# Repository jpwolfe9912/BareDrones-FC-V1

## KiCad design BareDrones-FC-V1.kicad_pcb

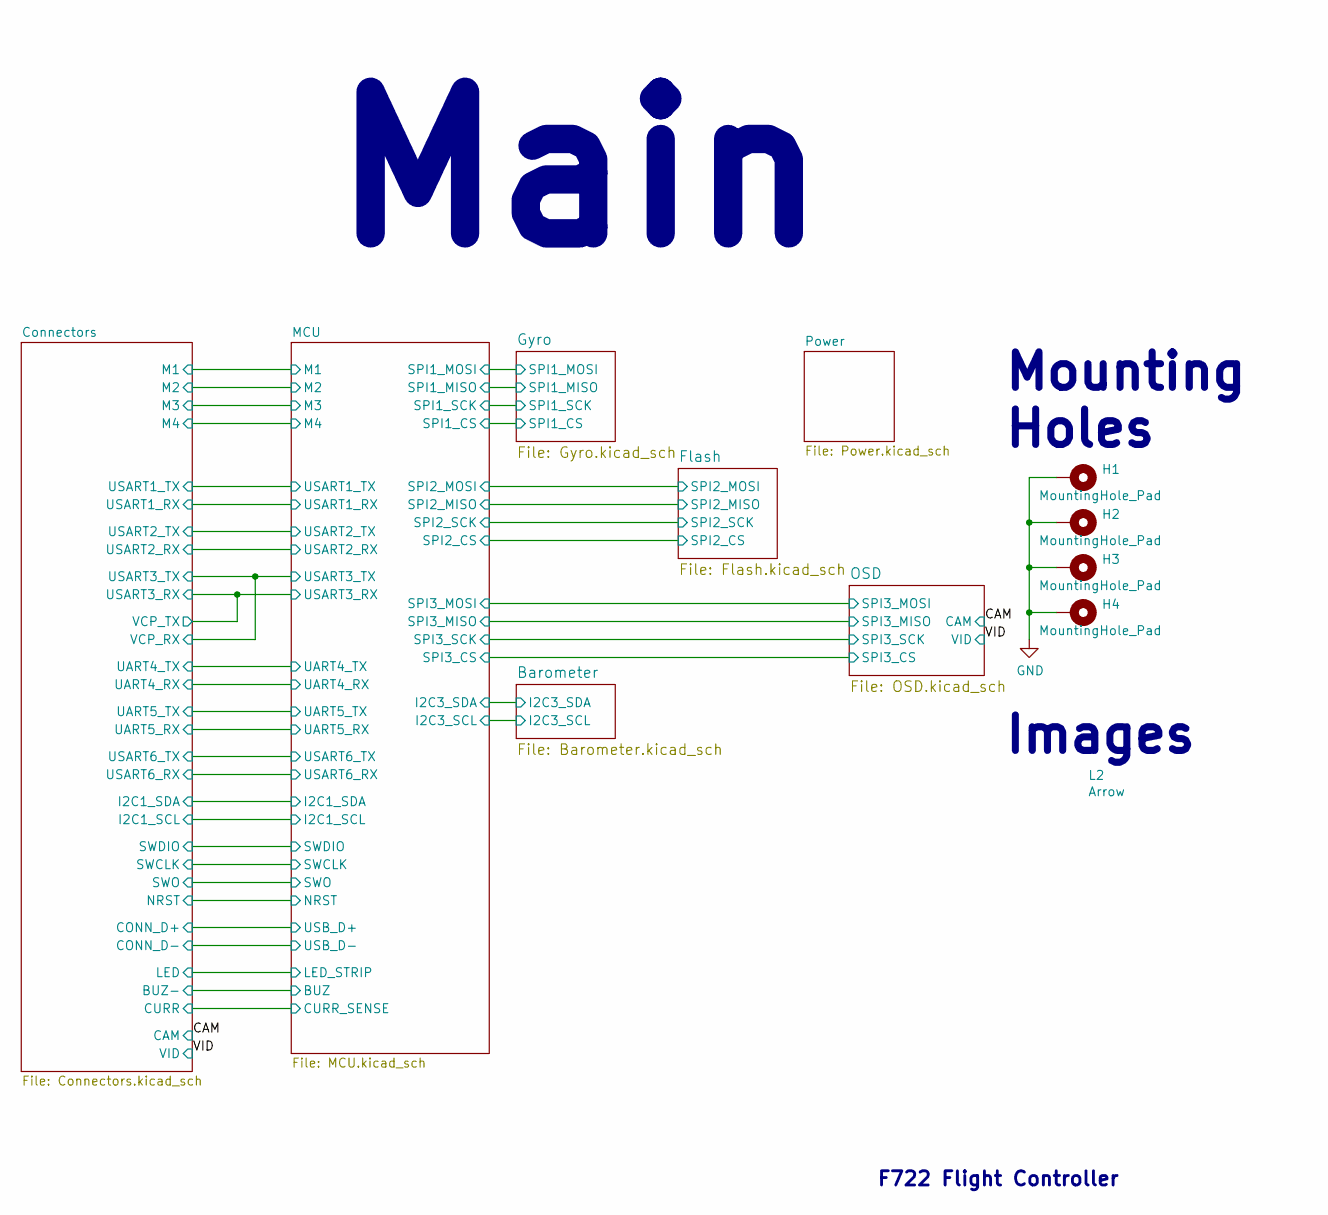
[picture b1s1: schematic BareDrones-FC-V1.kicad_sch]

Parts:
H1, H2, H3, H4: MountingHole_Pad; M3_Mounting_Hole
L1: EGA
L2: Arrow

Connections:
GND: H1.1, H2.1, H3.1, H4.1; also elsewhere on the board

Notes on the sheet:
F722 Flight Controller
Mounting Holes
Main
Images

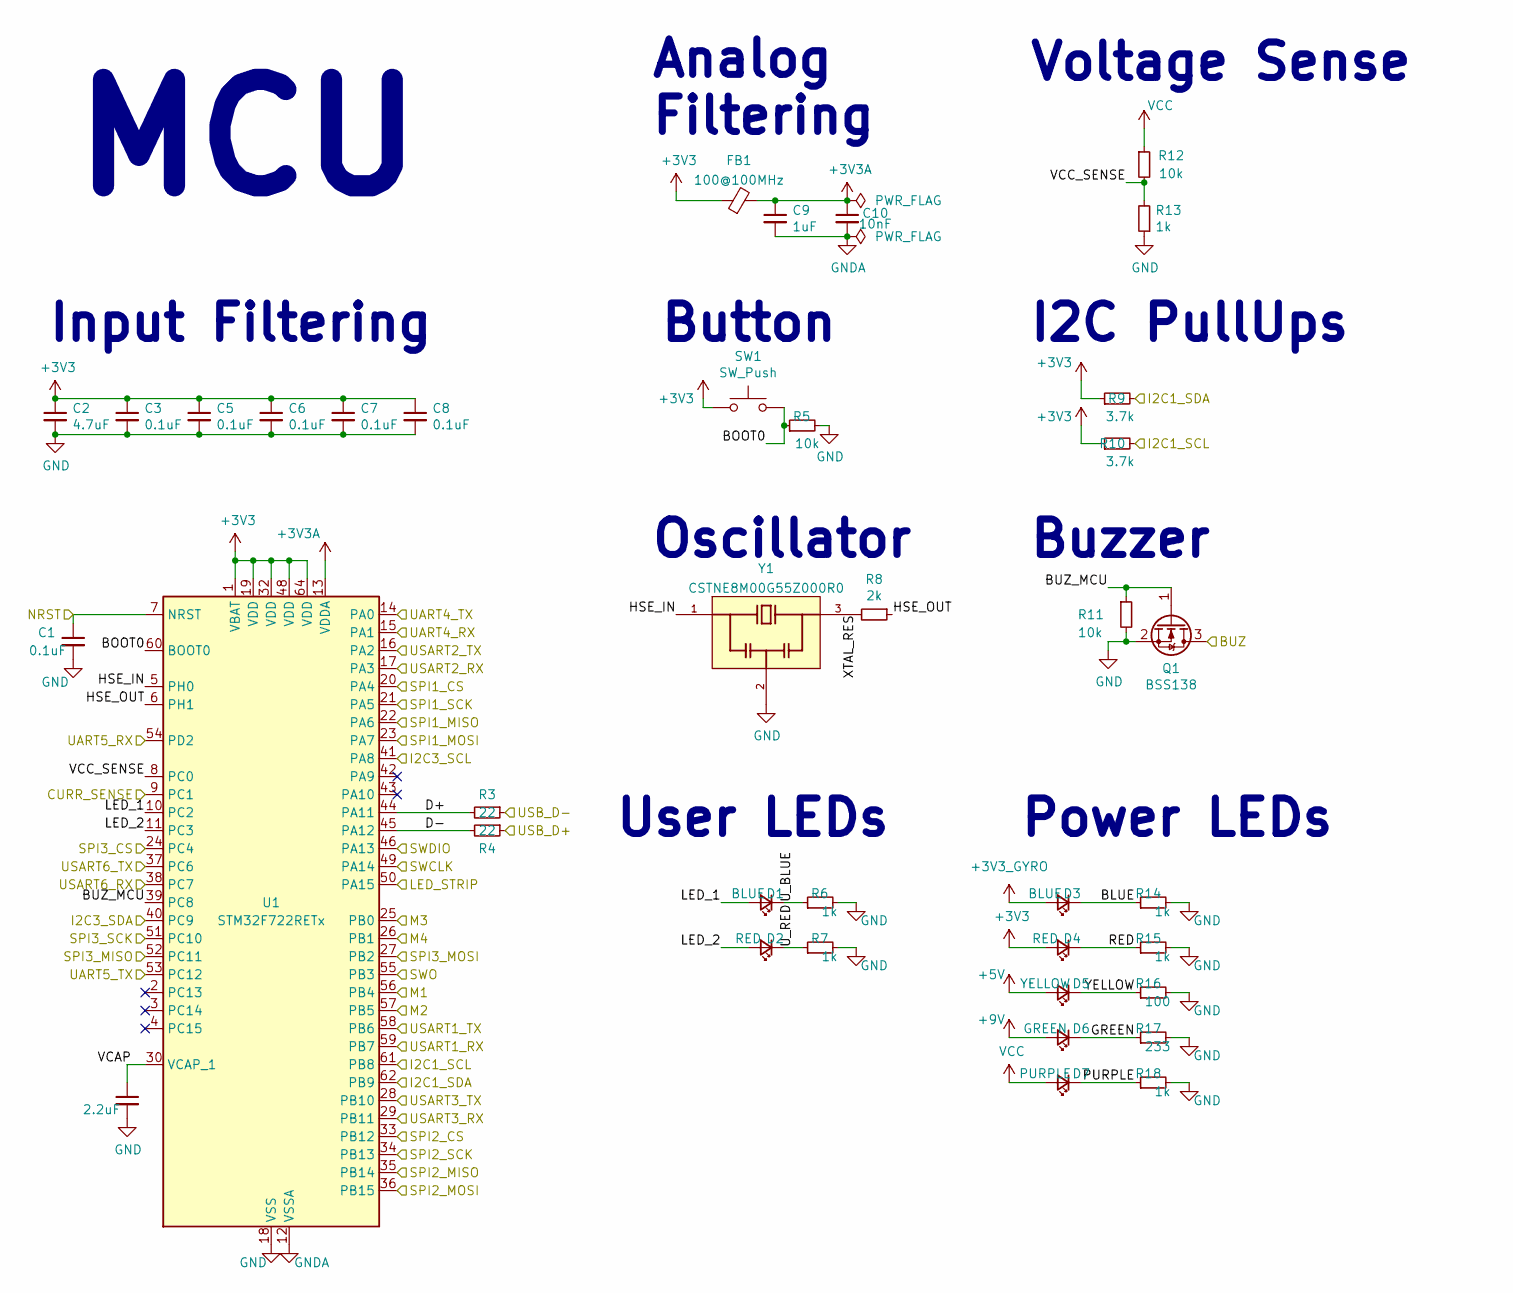
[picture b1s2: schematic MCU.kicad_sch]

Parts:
C1, C3, C5, C6, C7, C8: 0.1uF; C_0402_1005Metric
C2: 4.7uF; C_0402_1005Metric
C4: 2.2uF; C_0402_1005Metric
C9: 1uF; C_0402_1005Metric
C10: 10nF; C_0402_1005Metric
D1, D3: BLUE; LED_0603_1608Metric
D2, D4: RED; LED_0603_1608Metric
D5: YELLOW; LED_0603_1608Metric
D6: GREEN; LED_0603_1608Metric
D7: PURPLE; LED_0603_1608Metric
FB1: 100@100MHz; L_0603_1608Metric
Q1: BSS138; SOT-23
R3, R4: 22; R_0402_1005Metric
R5, R11, R12: 10k; R_0402_1005Metric
R6, R7, R13, R14, R15, R18: 1k; R_0402_1005Metric
R8: 2k; R_0402_1005Metric
R9, R10: 3.7k; R_0402_1005Metric
R16: 100; R_0402_1005Metric
R17: 233; R_0402_1005Metric
SW1: SW_Push; SW_SPST_B3U-1000P
U1: STM32F722RETx; LQFP-64_10x10mm_P0.5mm
Y1: CSTNE8M00G55Z000R0; OSC_CSTNE8M00G55Z000R0; PARTREV JGC42-8858A

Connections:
+3V3: C2.1, C3.1, C5.1, C6.1, C7.1, C8.1, D4.2 (A), FB1.1, R9.1, R10.1, SW1.1, U1.1 (VBAT), U1.19 (VDD), U1.32 (VDD), U1.48 (VDD), U1.64 (VDD); also elsewhere on the board
+3V3A: C9.1, C10.1, FB1.2, U1.13 (VDDA)
+3V3_GYRO: D3.2 (A); also elsewhere on the board
+5V: D5.2 (A); also elsewhere on the board
+9V: D6.2 (A); also elsewhere on the board
/Barometer/I2C3_SCL: U1.41 (PA8); also elsewhere on the board
/Barometer/I2C3_SDA: U1.40 (PC9); also elsewhere on the board
/Connectors/BUZ-: Q1.3 (D); also elsewhere on the board
/Connectors/CONN_D+: R4.1; also elsewhere on the board
/Connectors/CONN_D-: R3.1; also elsewhere on the board
/Connectors/CURR: U1.9 (PC1); also elsewhere on the board
/Connectors/I2C1_SCL: R10.2, U1.61 (PB8); also elsewhere on the board
/Connectors/I2C1_SDA: R9.2, U1.62 (PB9); also elsewhere on the board
/Connectors/LED: U1.50 (PA15); also elsewhere on the board
/Connectors/M1: U1.56 (PB4); also elsewhere on the board
/Connectors/M2: U1.57 (PB5); also elsewhere on the board
/Connectors/M3: U1.25 (PB0); also elsewhere on the board
/Connectors/M4: U1.26 (PB1); also elsewhere on the board
/Connectors/NRST: C1.1, U1.7 (NRST); also elsewhere on the board
/Connectors/SWCLK: U1.49 (PA14); also elsewhere on the board
/Connectors/SWDIO: U1.46 (PA13); also elsewhere on the board
/Connectors/SWO: U1.55 (PB3); also elsewhere on the board
/Connectors/UART4_RX: U1.15 (PA1); also elsewhere on the board
/Connectors/UART4_TX: U1.14 (PA0); also elsewhere on the board
/Connectors/UART5_RX: U1.54 (PD2); also elsewhere on the board
/Connectors/UART5_TX: U1.53 (PC12); also elsewhere on the board
/Connectors/USART1_RX: U1.59 (PB7); also elsewhere on the board
/Connectors/USART1_TX: U1.58 (PB6); also elsewhere on the board
/Connectors/USART2_RX: U1.17 (PA3); also elsewhere on the board
/Connectors/USART2_TX: U1.16 (PA2); also elsewhere on the board
/Connectors/USART3_RX: U1.29 (PB11); also elsewhere on the board
/Connectors/USART3_TX: U1.28 (PB10); also elsewhere on the board
/Connectors/USART6_RX: U1.38 (PC7); also elsewhere on the board
/Connectors/USART6_TX: U1.37 (PC6); also elsewhere on the board
/Flash/SPI2_CS: U1.33 (PB12); also elsewhere on the board
/Flash/SPI2_MISO: U1.35 (PB14); also elsewhere on the board
/Flash/SPI2_MOSI: U1.36 (PB15); also elsewhere on the board
/Flash/SPI2_SCK: U1.34 (PB13); also elsewhere on the board
/Gyro/SPI1_CS: U1.20 (PA4); also elsewhere on the board
/Gyro/SPI1_MISO: U1.22 (PA6); also elsewhere on the board
/Gyro/SPI1_MOSI: U1.23 (PA7); also elsewhere on the board
/Gyro/SPI1_SCK: U1.21 (PA5); also elsewhere on the board
/MCU/BLUE: D3.1 (K), R14.1
/MCU/BOOT0: R5.1, SW1.2, U1.60 (BOOT0)
/MCU/BUZ_MCU: Q1.1 (G), R11.1, U1.39 (PC8)
/MCU/D+: R3.2, U1.44 (PA11)
/MCU/D-: R4.2, U1.45 (PA12)
/MCU/GREEN: D6.1 (K), R17.1
/MCU/HSE_IN: U1.5 (PH0), Y1.1
/MCU/HSE_OUT: R8.1, U1.6 (PH1)
/MCU/LED_1: D1.2 (A), U1.10 (PC2)
/MCU/LED_2: D2.2 (A), U1.11 (PC3)
/MCU/PURPLE: D7.1 (K), R18.1
/MCU/RED: D4.1 (K), R15.1
/MCU/SPI3_CS: U1.24 (PC4); also elsewhere on the board
/MCU/SPI3_MISO: U1.52 (PC11); also elsewhere on the board
/MCU/SPI3_MOSI: U1.27 (PB2); also elsewhere on the board
/MCU/SPI3_SCK: U1.51 (PC10); also elsewhere on the board
/MCU/U_BLUE: D1.1 (K), R6.1
/MCU/U_RED: D2.1 (K), R7.1
/MCU/VCAP: C4.1, U1.30 (VCAP_1)
/MCU/VCC_SENSE: R12.2, R13.2, U1.8 (PC0)
/MCU/XTAL_RES: R8.2, Y1.3
/MCU/YELLOW: D5.1 (K), R16.1
GND: C1.2, C2.2, C3.2, C4.2, C5.2, C6.2, C7.2, C8.2, Q1.2 (S), R5.2, R6.2, R7.2, R11.2, R13.1, R14.2, R15.2, R16.2, R17.2, R18.2, U1.18 (VSS), U1.31 (VSS), U1.47 (VSS), U1.63 (VSS), Y1.2; also elsewhere on the board
GNDA: C9.2, C10.2, U1.12 (VSSA)
VCC: D7.2 (A), R12.1; also elsewhere on the board

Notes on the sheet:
MCU
User LEDs
Buzzer
Analog Filtering
Input Filtering
Oscillator
I2C PullUps
Button
Voltage Sense
Power LEDs

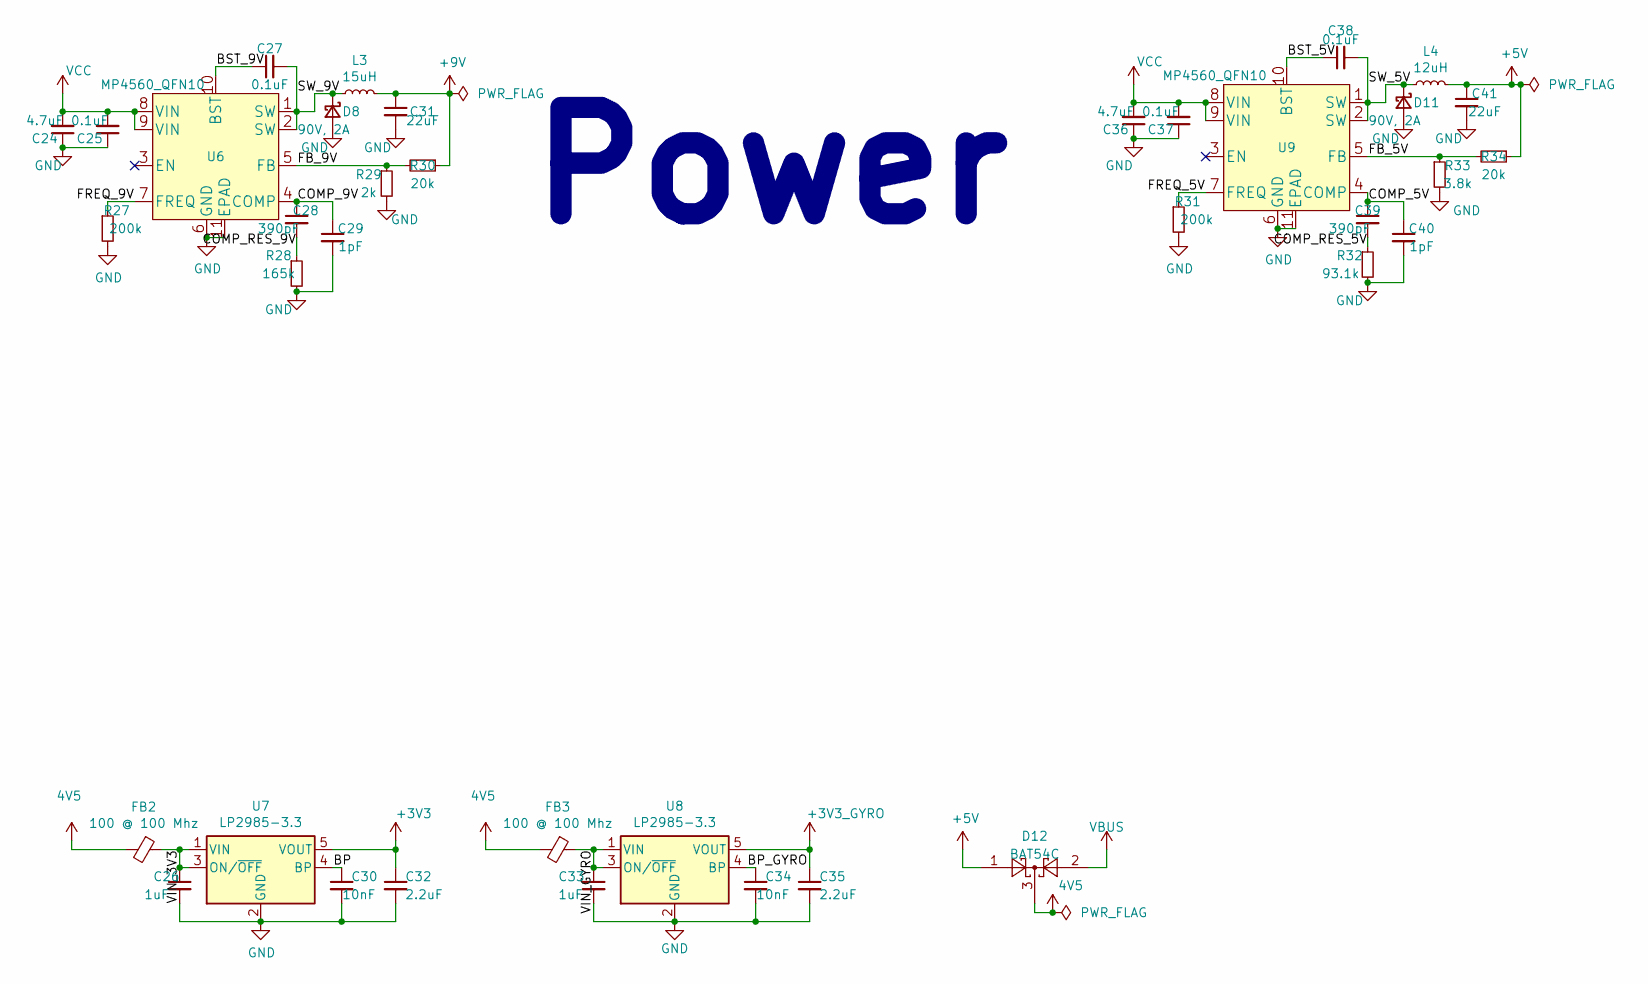
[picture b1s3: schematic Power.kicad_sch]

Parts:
C24, C36: 4.7uF; C_0402_1005Metric
C25, C27, C37, C38: 0.1uF; C_0402_1005Metric
C26, C33: 1uF; C_0402_1005Metric
C28, C39: 390pF; C_0402_1005Metric
C29, C40: 1pF; C_0402_1005Metric
C30, C34: 10nF; C_0402_1005Metric
C31, C41: 22uF; C_0402_1005Metric
C32, C35: 2.2uF; C_0402_1005Metric
D8, D11: 90V, 2A; D_SOD-523
D12: BAT54C; SOT-23
FB2, FB3: 100 @ 100 Mhz; L_0603_1608Metric
L3: 15uH; SRN3015-4R7M
L4: 12uH; SRN3015-4R7M
R27, R31: 200k; R_0402_1005Metric
R28: 165k; R_0402_1005Metric
R29: 2k; R_0402_1005Metric
R30, R34: 20k; R_0402_1005Metric
R32: 93.1k; R_0402_1005Metric
R33: 3.8k; R_0402_1005Metric
U6, U9: MP4560_QFN10; MP4560DQ
U7, U8: LP2985-3.3; SOT-23-5

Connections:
4V5: D12.3, FB2.2, FB3.2; also elsewhere on the board
+3V3: C32.1, U7.5 (VOUT); also elsewhere on the board
+3V3_GYRO: C35.1, U8.5 (VOUT); also elsewhere on the board
+5V: C41.1, D12.1, L4.2, R34.1; also elsewhere on the board
+9V: C31.1, L3.2, R30.1; also elsewhere on the board
/Power/BP: C30.1, U7.4 (BP)
/Power/BP_GYRO: C34.1, U8.4 (BP)
/Power/BST_5V: C38.1, U9.10 (BST)
/Power/BST_9V: C27.1, U6.10 (BST)
/Power/COMP_5V: C39.1, C40.1, U9.4 (COMP)
/Power/COMP_9V: C28.1, C29.1, U6.4 (COMP)
/Power/COMP_RES_5V: C39.2, R32.1
/Power/COMP_RES_9V: C28.2, R28.1
/Power/FB_5V: R33.1, R34.2, U9.5 (FB)
/Power/FB_9V: R29.1, R30.2, U6.5 (FB)
/Power/FREQ_5V: R31.1, U9.7 (FREQ)
/Power/FREQ_9V: R27.1, U6.7 (FREQ)
/Power/SW_5V: C38.2, D11.1 (K), L4.1, U9.1 (SW), U9.2 (SW)
/Power/SW_9V: C27.2, D8.1 (K), L3.1, U6.1 (SW), U6.2 (SW)
/Power/VIN_3V3: C26.1, FB2.1, U7.1 (VIN), U7.3 (ON/~OFF)
/Power/VIN_GYRO: C33.1, FB3.1, U8.1 (VIN), U8.3 (ON/~OFF)
GND: C24.1, C25.1, C26.2, C29.2, C30.2, C31.2, C32.2, C33.2, C34.2, C35.2, C36.1, C37.1, C40.2, C41.2, D8.2 (A), D11.2 (A), R27.2, R28.2, R29.2, R31.2, R32.2, R33.2, U6.6 (GND), U6.11 (EPAD), U7.2 (GND), U8.2 (GND), U9.6 (GND), U9.11 (EPAD); also elsewhere on the board
VBUS: D12.2; also elsewhere on the board
VCC: C24.2, C25.2, C36.2, C37.2, U6.8 (VIN), U6.9 (VIN), U9.8 (VIN), U9.9 (VIN); also elsewhere on the board

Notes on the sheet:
Power

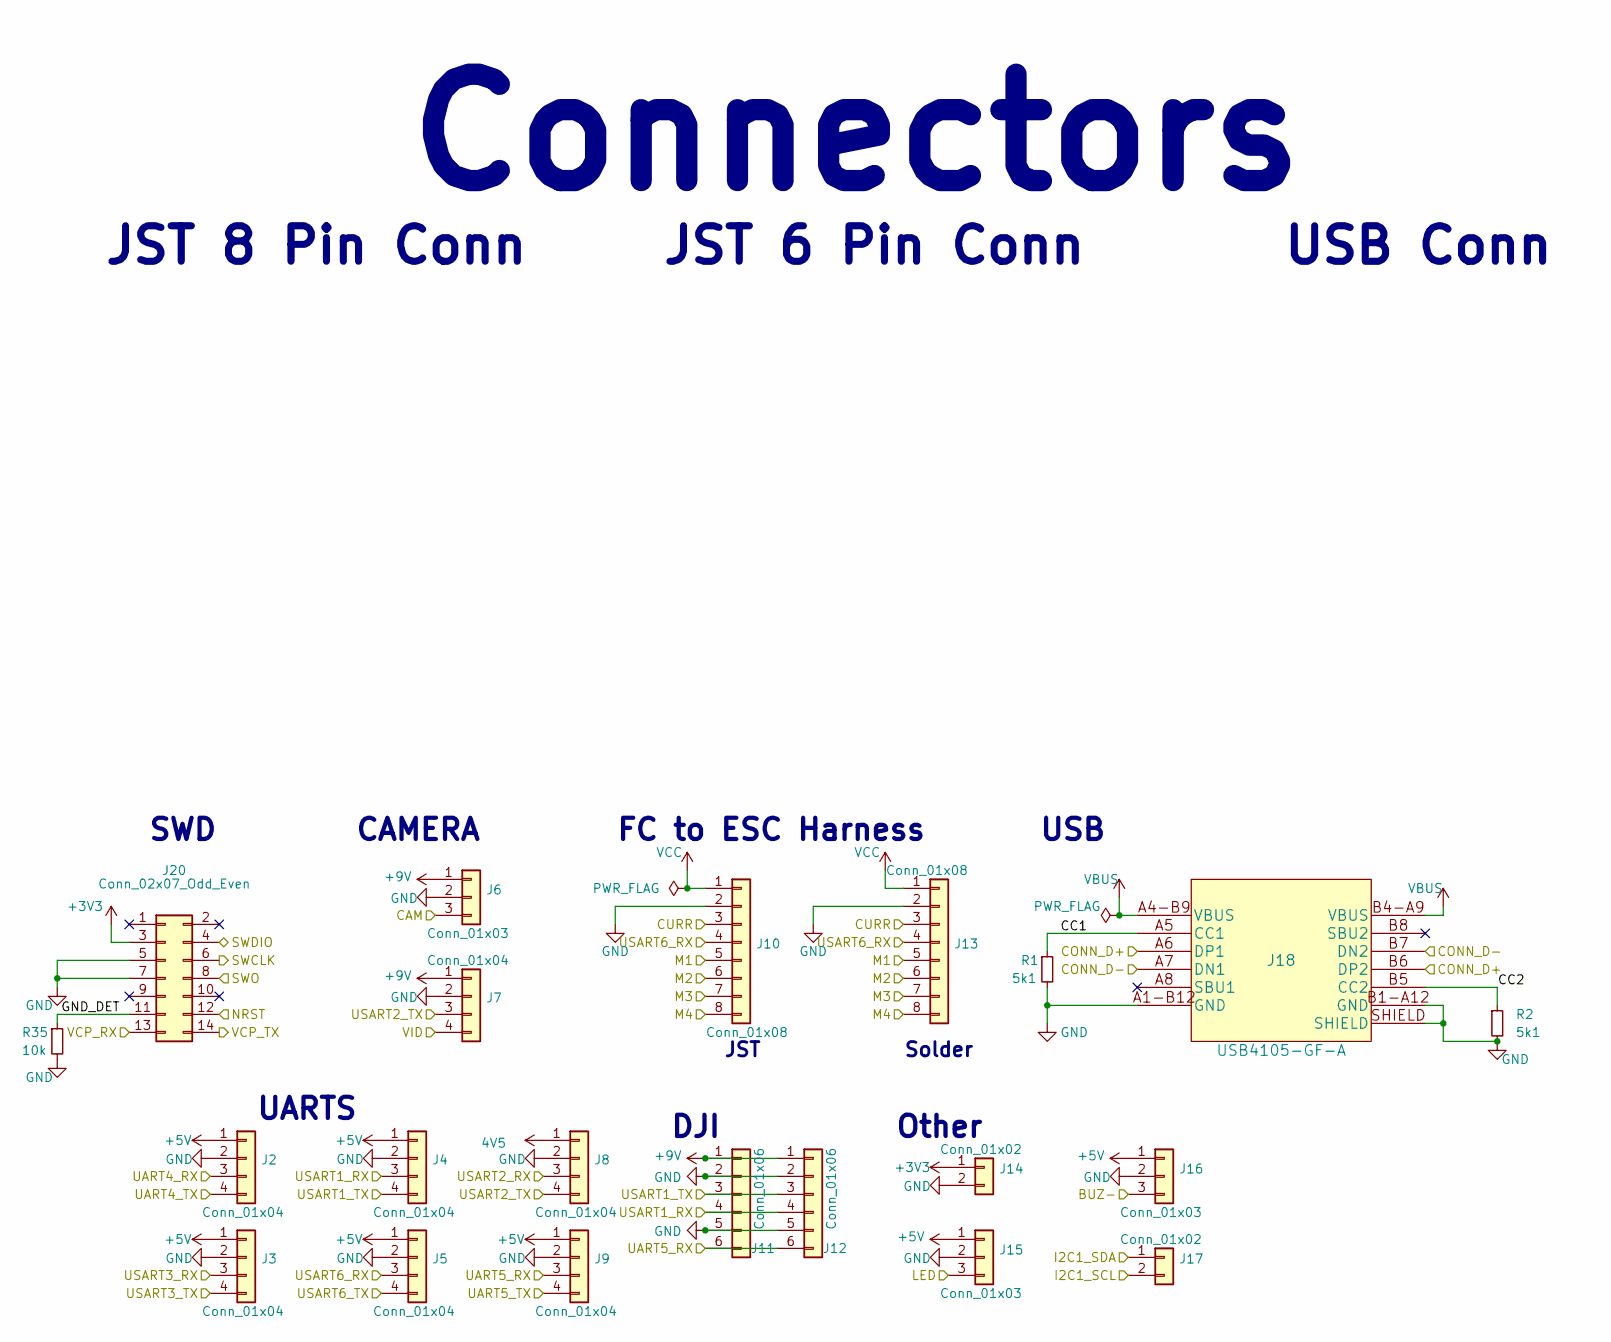
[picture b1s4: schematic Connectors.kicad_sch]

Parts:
J2, J3, J4, J5, J7, J8, J9: Conn_01x04; Conn_1x4_SMT
J6, J15, J16: Conn_01x03; Conn_1x3_SMT
J10: Conn_01x08; JST_SH_SM08B-SRSS-TB_1x08-1MP_P1.00mm_Horizontal
J11: Conn_01x06; JST_SH_SM06B-SRSS-TB_1x06-1MP_P1.00mm_Horizontal
J12: Conn_01x06; Conn_DJI
J13: Conn_01x08; Conn_8Edge_SMT
J14, J17: Conn_01x02; Conn_1x2_SMT
J18: USB4105-GF-A; GCT_USB4105-GF-A
J20: Conn_02x07_Odd_Even; PinHeader_2x07_P1.27mm_Vertical_SMD
R1, R2: 5k1; R_0402_1005Metric
R35: 10k; R_0402_1005Metric

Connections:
4V5: J8.1; also elsewhere on the board
+3V3: J14.1, J20.3; also elsewhere on the board
+5V: J2.1, J3.1, J4.1, J5.1, J9.1, J15.1, J16.1; also elsewhere on the board
+9V: J6.1, J7.1, J11.1, J12.1; also elsewhere on the board
/CAM: J6.3; also elsewhere on the board
/Connectors/BUZ-: J16.3; also elsewhere on the board
/Connectors/CC1: J18.A5 (CC1), R1.1
/Connectors/CC2: J18.B5 (CC2), R2.1
/Connectors/CONN_D+: J18.A6 (DP1), J18.B6 (DP2); also elsewhere on the board
/Connectors/CONN_D-: J18.A7 (DN1), J18.B7 (DN2); also elsewhere on the board
/Connectors/CURR: J10.3, J13.3; also elsewhere on the board
/Connectors/GND_DET: J20.11, R35.1
/Connectors/I2C1_SCL: J17.2; also elsewhere on the board
/Connectors/I2C1_SDA: J17.1; also elsewhere on the board
/Connectors/LED: J15.3; also elsewhere on the board
/Connectors/M1: J10.5, J13.5; also elsewhere on the board
/Connectors/M2: J10.6, J13.6; also elsewhere on the board
/Connectors/M3: J10.7, J13.7; also elsewhere on the board
/Connectors/M4: J10.8, J13.8; also elsewhere on the board
/Connectors/NRST: J20.12; also elsewhere on the board
/Connectors/SWCLK: J20.6; also elsewhere on the board
/Connectors/SWDIO: J20.4; also elsewhere on the board
/Connectors/SWO: J20.8; also elsewhere on the board
/Connectors/UART4_RX: J2.3; also elsewhere on the board
/Connectors/UART4_TX: J2.4; also elsewhere on the board
/Connectors/UART5_RX: J9.3, J11.6, J12.6; also elsewhere on the board
/Connectors/UART5_TX: J9.4; also elsewhere on the board
/Connectors/USART1_RX: J4.3, J11.4, J12.4; also elsewhere on the board
/Connectors/USART1_TX: J4.4, J11.3, J12.3; also elsewhere on the board
/Connectors/USART2_RX: J8.3; also elsewhere on the board
/Connectors/USART2_TX: J7.3, J8.4; also elsewhere on the board
/Connectors/USART3_RX: J3.3, J20.14; also elsewhere on the board
/Connectors/USART3_TX: J3.4, J20.13; also elsewhere on the board
/Connectors/USART6_RX: J5.3, J10.4, J13.4; also elsewhere on the board
/Connectors/USART6_TX: J5.4; also elsewhere on the board
/VID: J7.4; also elsewhere on the board
GND: J2.2, J3.2, J4.2, J5.2, J6.2, J7.2, J8.2, J9.2, J10.2, J11.2, J11.5, J12.2, J12.5, J13.2, J14.2, J15.2, J16.2, J18.A1-B12 (GND), J18.B1-A12 (GND), J18.SHIELD, J20.5, J20.7, R1.2, R2.2, R35.2; also elsewhere on the board
VBUS: J18.A4-B9 (VBUS), J18.B4-A9 (VBUS); also elsewhere on the board
VCC: J10.1, J13.1; also elsewhere on the board

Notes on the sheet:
JST 6 Pin Conn
Solder
JST
Connectors
CAMERA
Other
JST 8 Pin Conn
DJI
USB Conn
USB
UARTS
FC to ESC Harness
SWD

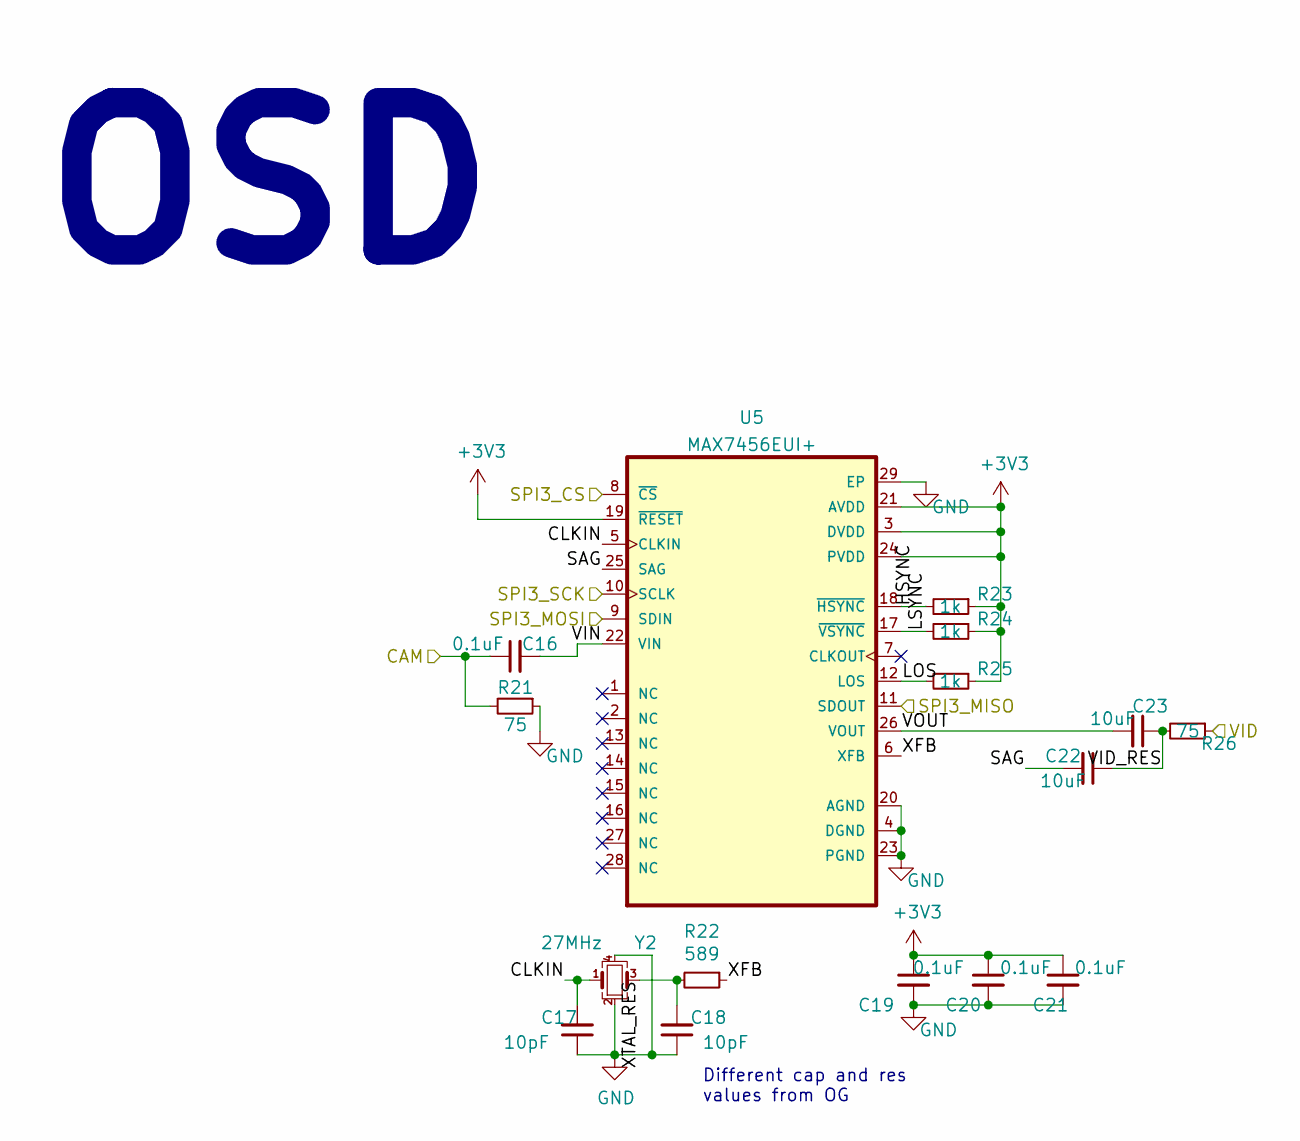
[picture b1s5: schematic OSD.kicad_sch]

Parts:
C16, C19, C20, C21: 0.1uF; C_0402_1005Metric
C17, C18: 10pF; C_0402_1005Metric
C22, C23: 10uF; C_0402_1005Metric
R21, R26: 75; R_0402_1005Metric
R22: 589; R_0402_1005Metric
R23, R24, R25: 1k; R_0402_1005Metric
U5: MAX7456EUI+; MAX7456
Y2: 27MHz; Oscillator_SMD_Abracon_ASE-4Pin_3.2x2.5mm

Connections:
+3V3: C19.1, C20.1, C21.1, R23.1, R24.1, R25.1, U5.3 (DVDD), U5.19 (~RESET), U5.21 (AVDD), U5.24 (PVDD); also elsewhere on the board
/CAM: C16.1, R21.2; also elsewhere on the board
/MCU/SPI3_CS: U5.8 (~CS); also elsewhere on the board
/MCU/SPI3_MISO: U5.11 (SDOUT); also elsewhere on the board
/MCU/SPI3_MOSI: U5.9 (SDIN); also elsewhere on the board
/MCU/SPI3_SCK: U5.10 (SCLK); also elsewhere on the board
/OSD/CLKIN: C17.2, U5.5 (CLKIN), Y2.1
/OSD/HSYNC: R23.2, U5.18 (~HSYNC)
/OSD/LOS: R25.2, U5.12 (LOS)
/OSD/LSYNC: R24.2, U5.17 (~VSYNC)
/OSD/SAG: C22.2, U5.25 (SAG)
/OSD/VID_RES: C22.1, C23.1, R26.2
/OSD/VIN: C16.2, U5.22 (VIN)
/OSD/VOUT: C23.2, U5.26 (VOUT)
/OSD/XFB: R22.1, U5.6 (XFB)
/OSD/XTAL_RES: C18.2, R22.2, Y2.3
/VID: R26.1; also elsewhere on the board
GND: C17.1, C18.1, C19.2, C20.2, C21.2, R21.1, U5.4 (DGND), U5.20 (AGND), U5.23 (PGND), U5.29 (EP), Y2.2, Y2.4; also elsewhere on the board

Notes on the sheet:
Different cap and res values from OG
OSD

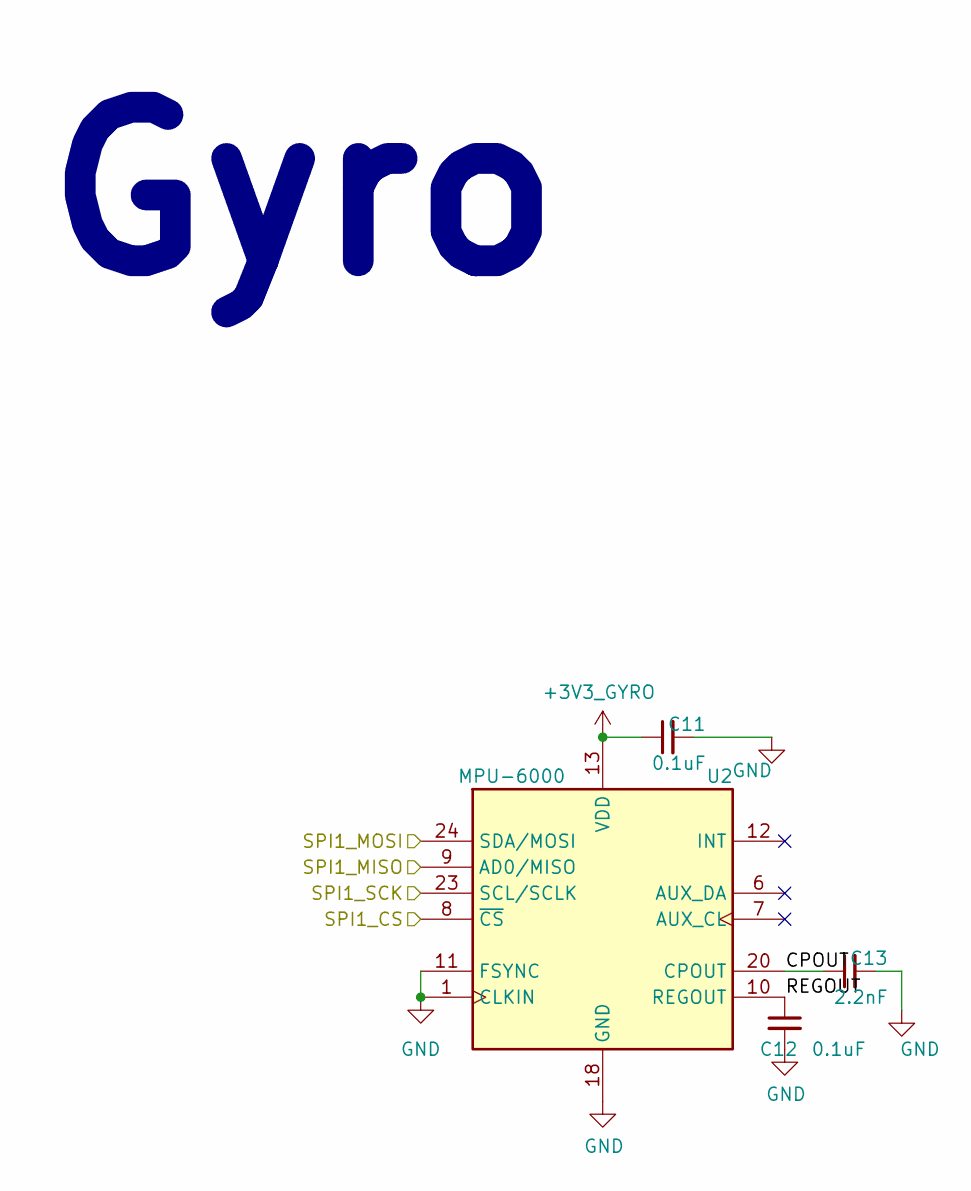
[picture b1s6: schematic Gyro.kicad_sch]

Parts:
C11, C12: 0.1uF; C_0402_1005Metric
C13: 2.2nF; C_0402_1005Metric
U2: MPU-6000; InvenSense_QFN-24_4x4mm_P0.5mm

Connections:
+3V3_GYRO: C11.1, U2.13 (VDD); also elsewhere on the board
/Gyro/CPOUT: C13.1, U2.20 (CPOUT)
/Gyro/REGOUT: C12.1, U2.10 (REGOUT)
/Gyro/SPI1_CS: U2.8 (~CS); also elsewhere on the board
/Gyro/SPI1_MISO: U2.9 (AD0/MISO); also elsewhere on the board
/Gyro/SPI1_MOSI: U2.24 (SDA/MOSI); also elsewhere on the board
/Gyro/SPI1_SCK: U2.23 (SCL/SCLK); also elsewhere on the board
GND: C11.2, C12.2, C13.2, U2.1 (CLKIN), U2.11 (FSYNC), U2.18 (GND); also elsewhere on the board

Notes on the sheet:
Gyro

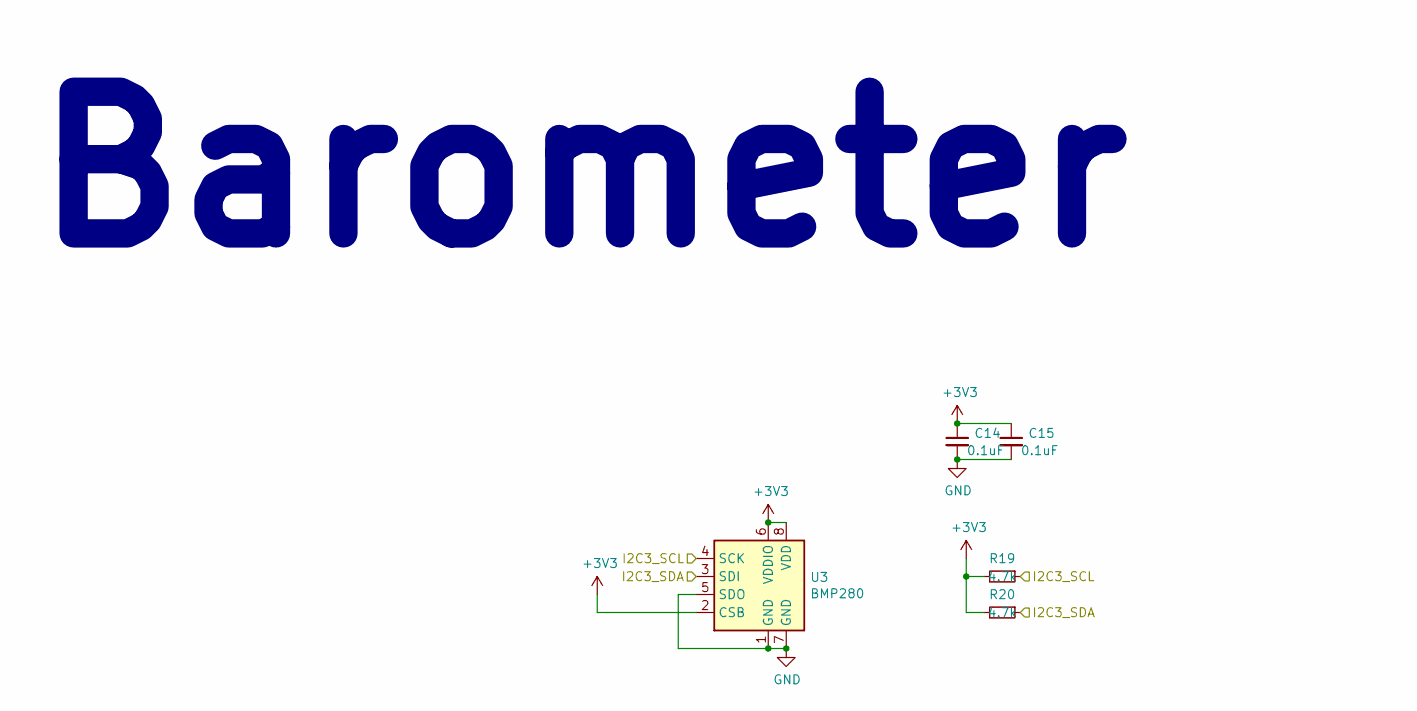
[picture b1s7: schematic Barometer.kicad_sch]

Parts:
C14, C15: 0.1uF; C_0402_1005Metric
R19, R20: 4.7k; R_0402_1005Metric
U3: BMP280; Bosch_LGA-8_2x2.5mm_P0.65mm_ClockwisePinNumbering

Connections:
+3V3: C14.1, C15.1, R19.2, R20.2, U3.2 (CSB), U3.6 (VDDIO), U3.8 (VDD); also elsewhere on the board
/Barometer/I2C3_SCL: R19.1, U3.4 (SCK); also elsewhere on the board
/Barometer/I2C3_SDA: R20.1, U3.3 (SDI); also elsewhere on the board
GND: C14.2, C15.2, U3.1 (GND), U3.5 (SDO), U3.7 (GND); also elsewhere on the board

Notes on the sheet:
Barometer

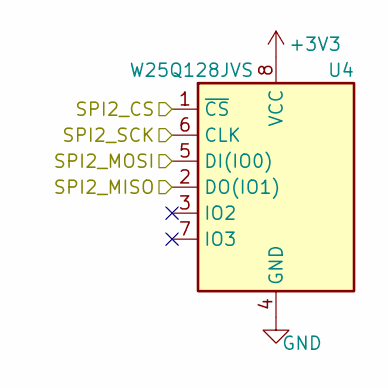
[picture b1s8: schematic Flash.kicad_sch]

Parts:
U4: W25Q128JVS; SOIC-8_5.23x5.23mm_P1.27mm

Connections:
+3V3: U4.8 (VCC); also elsewhere on the board
/Flash/SPI2_CS: U4.1 (~CS); also elsewhere on the board
/Flash/SPI2_MISO: U4.2 (DO(IO1)); also elsewhere on the board
/Flash/SPI2_MOSI: U4.5 (DI(IO0)); also elsewhere on the board
/Flash/SPI2_SCK: U4.6 (CLK); also elsewhere on the board
GND: U4.4 (GND); also elsewhere on the board

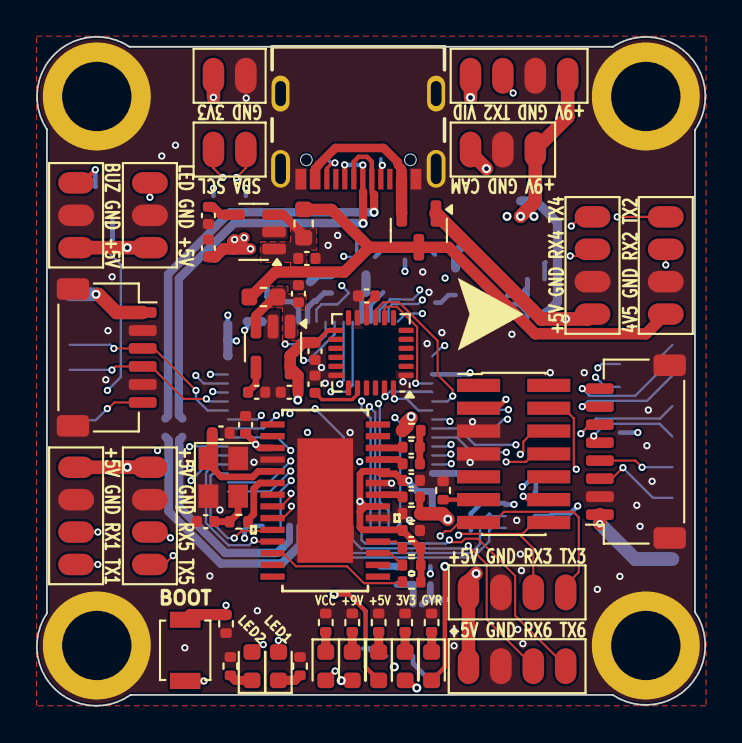
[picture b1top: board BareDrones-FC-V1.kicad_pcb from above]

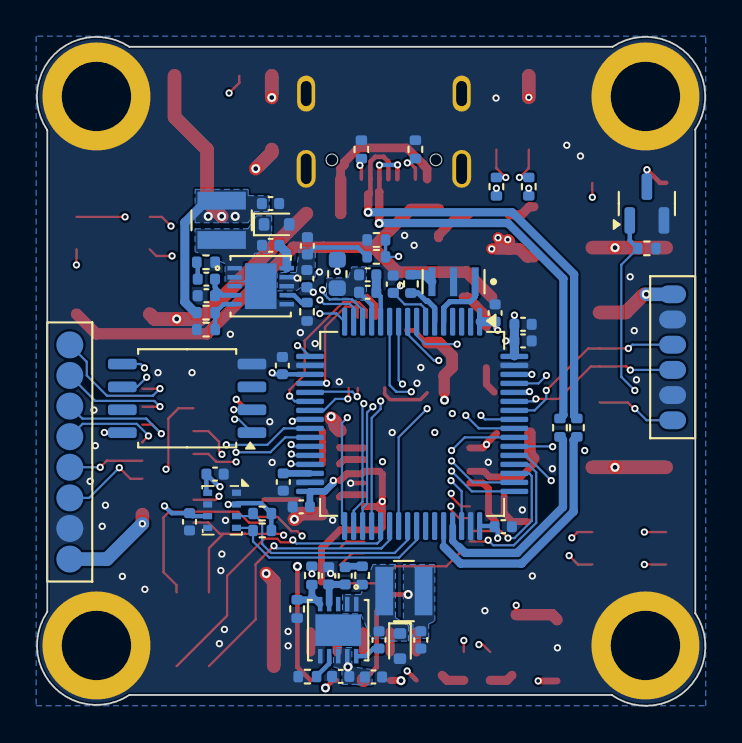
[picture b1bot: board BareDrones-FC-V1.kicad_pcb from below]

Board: 6 copper layers, 37.1 x 37.2 mm, 127 parts (58 on the bottom side), 102 nets.

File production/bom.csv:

Designator,Footprint,Quantity,Value,LCSC Part #
"C1, C11, C12, C14, C15, C16, C19, C20, C21, C25, C27, C3, C37, C38, C5, C6, C7, C8",0402,18,0.1uF,
"C10, C30, C34",0402,3,10nF,
C13,0402,1,2.2nF,
"C17, C18",0402,2,10pF,
"C2, C24, C36",0402,3,4.7uF,
"C22, C23",0402,2,10uF,
"C26, C33, C9",0402,3,1uF,
"C28, C39",0402,2,390pF,
"C29, C40",0402,2,1pF,
"C31, C41",0402,2,22uF,
"C32, C35, C4",0402,3,2.2uF,
"D1, D3",0603,2,BLUE,
"D11, D8",D_SOD-523,2,"90V, 2A",
D12,SOT-23,1,BAT54C,
"D2, D4",0603,2,RED,
D5,0603,1,YELLOW,
D6,0603,1,GREEN,
D7,0603,1,PURPLE,
FB1,0603,1,100@100MHz,
"FB2, FB3",0603,2,100 @ 100 Mhz,
"H1, H2, H3, H4",M3_Mounting_Hole,4,MountingHole_Pad,
J10,JST_SH_SM08B-SRSS-TB_1x08-1MP_P1.00mm_Horizontal,1,Conn_01x08,
J11,JST_SH_SM06B-SRSS-TB_1x06-1MP_P1.00mm_Horizontal,1,Conn_01x06,
J12,Conn_DJI,1,Conn_01x06,
J13,Conn_8Edge_SMT,1,Conn_01x08,
"J14, J17",Conn_1x2_SMT,2,Conn_01x02,
"J15, J16, J6",Conn_1x3_SMT,3,Conn_01x03,
J18,GCT_USB4105-GF-A,1,USB4105-GF-A,
"J2, J3, J4, J5, J7, J8, J9",Conn_1x4_SMT,7,Conn_01x04,
J20,PinHeader_2x07_P1.27mm_Vertical_SMD,1,Conn_02x07_Odd_Even,
L2,Arrow,1,Arrow,
L3,SRN3015-4R7M,1,15uH,
L4,SRN3015-4R7M,1,12uH,
Q1,SOT-23,1,BSS138,
"R1, R2",0402,2,5k1,
"R10, R9",0402,2,3.7k,
"R11, R12, R35, R5",0402,4,10k,
"R13, R14, R15, R18, R23, R24, R25, R6, R7",0402,9,1k,
R16,0402,1,100,
R17,0402,1,233,
"R19, R20",0402,2,4.7k,
"R21, R26",0402,2,75,
R22,0402,1,589,
"R27, R31",0402,2,200k,
R28,0402,1,165k,
"R29, R8",0402,2,2k,
"R3, R4",0402,2,22,
"R30, R34",0402,2,20k,
R32,0402,1,93.1k,
R33,0402,1,3.8k,
SW1,SW_SPST_B3U-1000P,1,SW_Push,
U1,LQFP-64_10x10mm_P0.5mm,1,STM32F722RETx,
U2,InvenSense_QFN-24_4x4mm_P0.5mm,1,MPU-6000,
U3,Bosch_LGA-8_2x2.5mm_P0.65mm_ClockwisePinNumbering,1,BMP280,
U4,SOIC-8_5.23x5.23mm_P1.27mm,1,W25Q128JVS,
U5,MAX7456,1,MAX7456EUI+,
"U6, U9",MP4560DQ,2,MP4560_QFN10,
"U7, U8",SOT-23-5,2,LP2985-3.3,
Y1,OSC_CSTNE8M00G55Z000R0,1,CSTNE8M00G55Z000R0,
Y2,Oscillator_SMD_Abracon_ASE-4Pin_3.2x2.5mm,1,27MHz,

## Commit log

2024-04-05 Finished power and signal routing.
2024-04-05 Finished connections
2024-04-06 Added Files
2024-04-06 Edited pics and reorganized
2024-04-06 Reorganized again
2024-04-06 Added gerber PDFs

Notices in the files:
parts and their libraries:
Copyright 2016 Accelerated Designs. All rights reserved.
Copyright 2021 Accelerated Designs. All rights reserved.
